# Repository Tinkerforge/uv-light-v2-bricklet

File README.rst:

UV Light Bricklet 2.0
=====================

This repository contains the firmware source code and the hardware design
files. The documentation generator configs can be found at
https://github.com/Tinkerforge/generators

Repository Content
------------------

software/:
 * examples/: Examples for all supported languages
 * build/: Compiled files
 * src/: Source code of firmware
 * Makefile: Makefile to build project

hardware/:
 * Contains KiCad project files and additionally schematics as PDF

datasheets/:
 * Contains datasheets for sensors and complex ICs that are used

Hardware
--------

The hardware is designed with the open source EDA Suite KiCad
(http://www.kicad.org). Before you are able to open the files,
you have to install the Tinkerforge kicad-libraries
(https://github.com/Tinkerforge/kicad-libraries). You can either clone
them directly in hardware/ or clone them in a separate folder and
symlink them into hardware/
(ln -s kicad_path/kicad-libraries project_path/hardware). After that you
can open the .pro file in hardware/ with KiCad and from there view and
modify the schematics and the PCB layout.

Software
--------

If you want to do your own Brick/Bricklet firmware development we highly
recommend that you use our build environment setup script and read the
tutorial (https://www.tinkerforge.com/en/doc/Tutorials/Tutorial_Build_Environment/Tutorial.html).

To compile the C code we recommend you to install the newest GNU Arm Embedded
Toolchain (https://launchpad.net/gcc-arm-embedded/+download).
You also need to install bricklib2 (https://github.com/Tinkerforge/bricklib2).

You can either clone it directly in software/src/ or clone it in a
separate folder and symlink it into software/src/
(ln -s bricklib_path/bricklib2 project_path/software/src/). Finally make sure to
have CMake installed (http://www.cmake.org/cmake/resources/software.html).

After that you can build the firmware by invoking make in software/.
The firmware (.zbin) can then be found in software/build/ and uploaded
with brickv (click button "Flashing" on start screen).

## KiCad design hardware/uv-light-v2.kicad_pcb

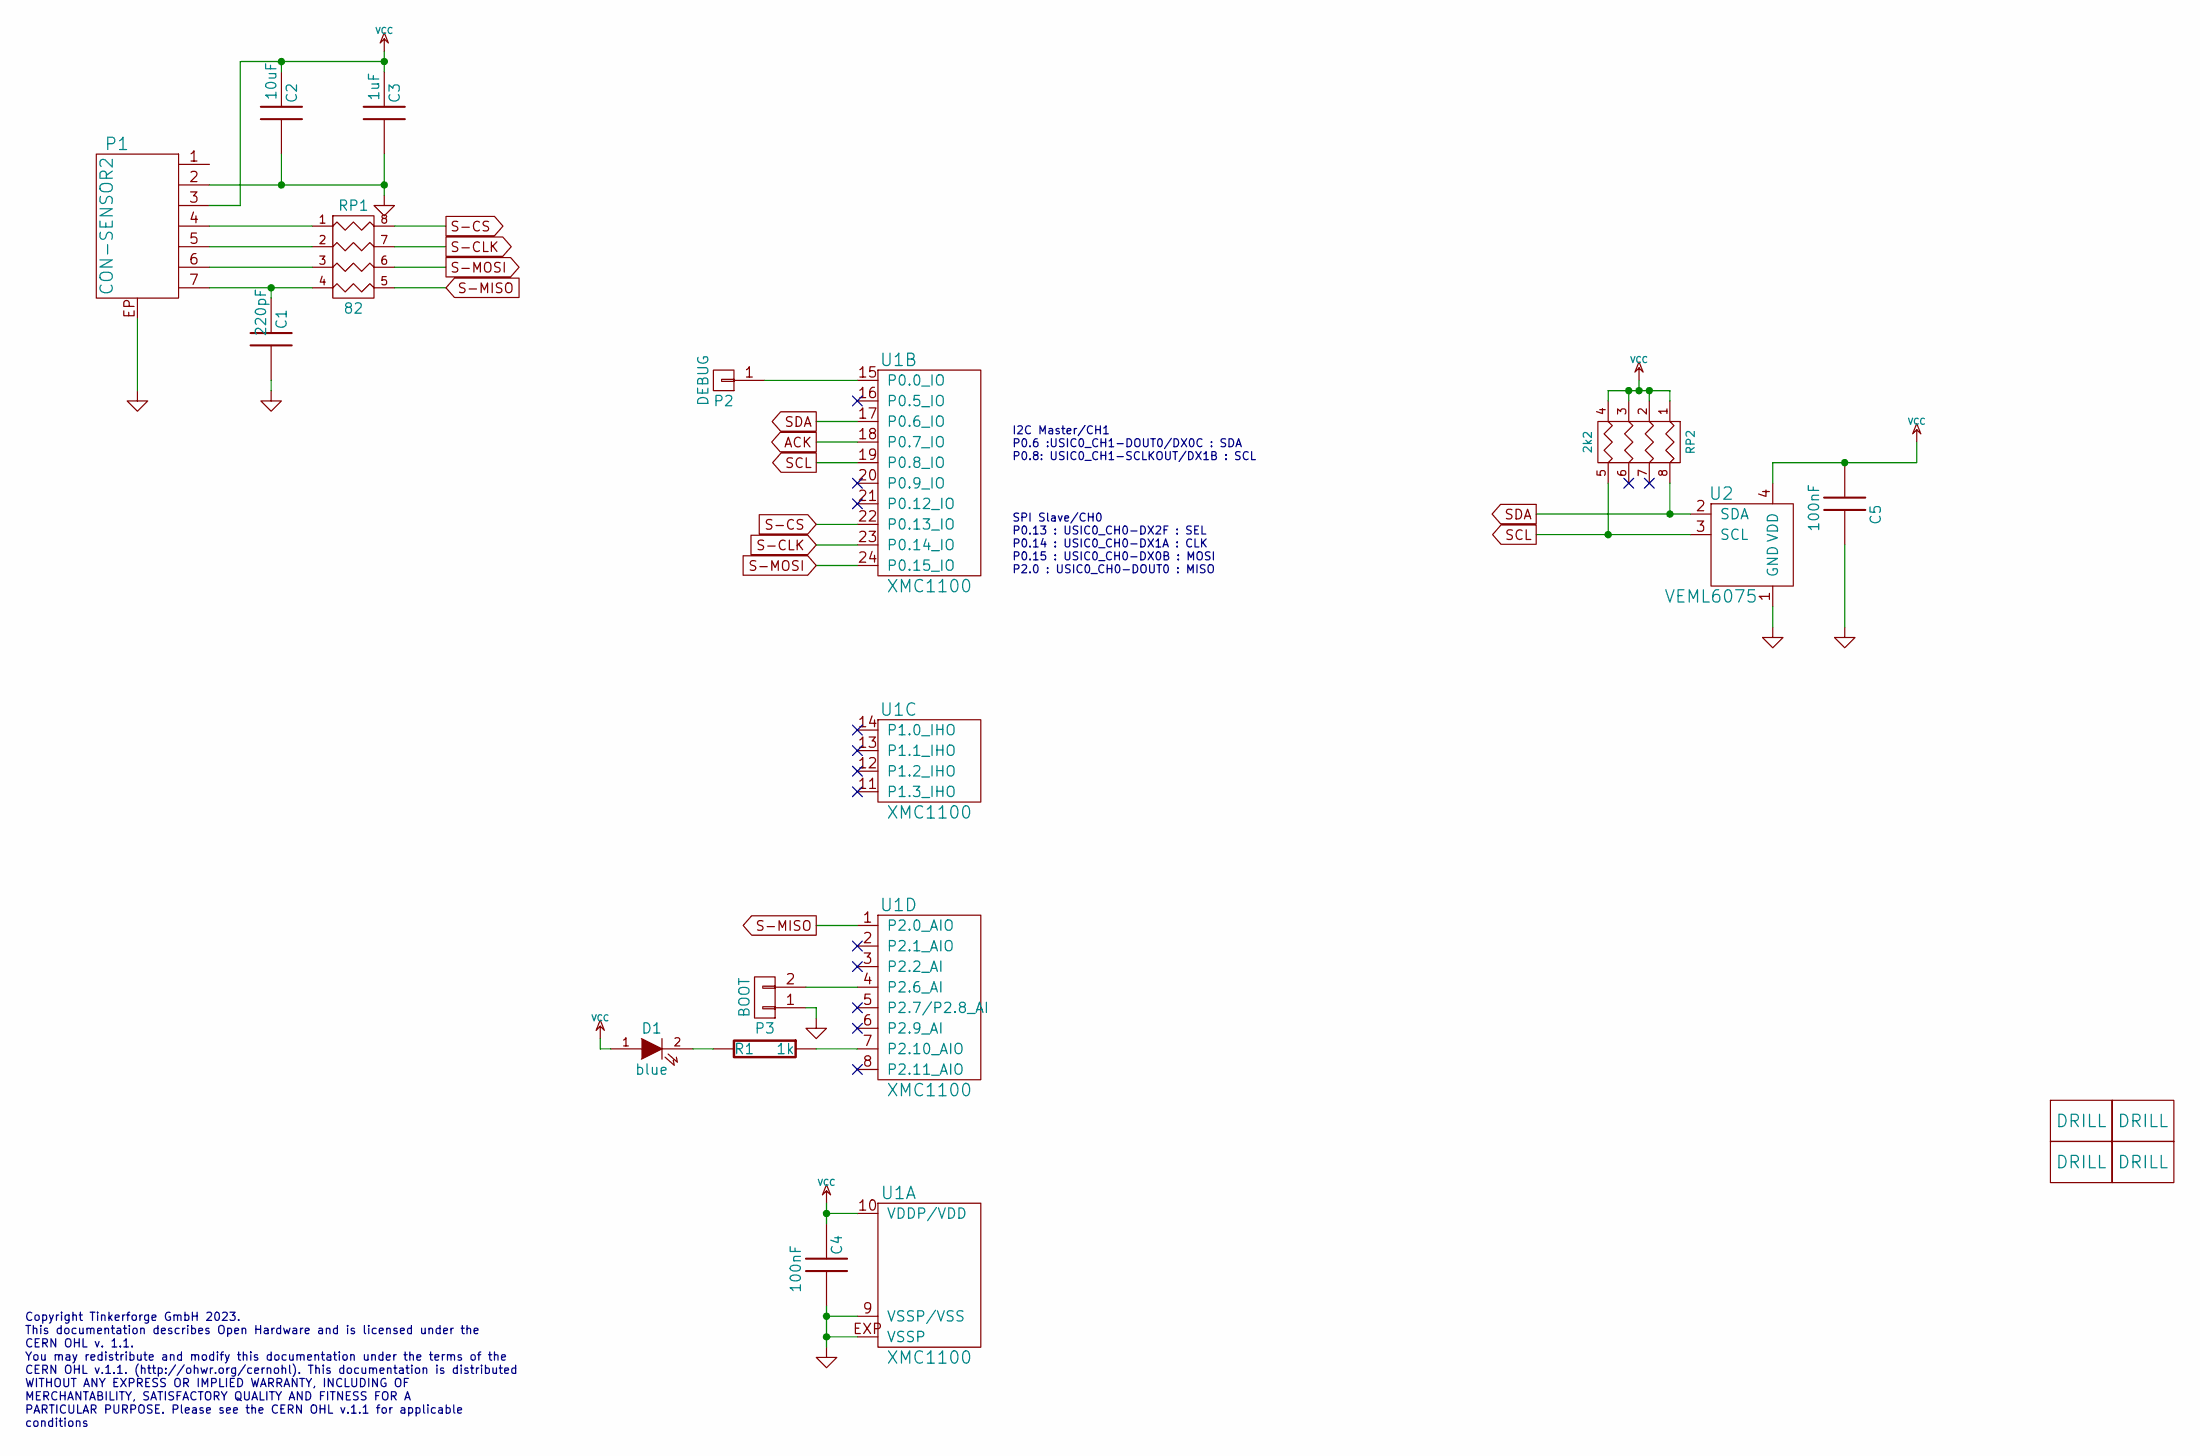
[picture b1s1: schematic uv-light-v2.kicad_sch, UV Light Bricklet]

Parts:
C1: 220pF; C0402F
C2: 10uF; C0805
C3: 1uF; C0603F
C4, C5: 100nF; C0603F
D1: blue; D0603F
P1: CON-SENSOR2
P2: DEBUG; DEBUG_PAD
P3: BOOT; SolderJumper
R1: 1k; R0603F
RP1: 82; 4X0402
RP2: 2k2; 0603X4
U1: XMC1100; QFN24-4x4mm-0.5mm
U2: VEML6075; OPLGA4
U3, U4, U5, U6: DRILL; DRILL_NP

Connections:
ACK: U1.18 (P0.7_IO)
GND: C1.1, C2.1, C3.1, C4.1, C5.1, P1.2, P1.EP, P3.1, U1.9 (VSSP/VSS), U1.EXP (VSSP), U2.1 (GND)
unnamed: C1.2, P1.7, RP1.4
unnamed: D1.2 (K), R1.2
unnamed: P1.4, RP1.1
unnamed: P1.5, RP1.2
unnamed: P1.6, RP1.3
unnamed: P2.1, U1.15 (P0.0_IO)
unnamed: P3.2, U1.4 (P2.6_AI)
unnamed: R1.1, U1.7 (P2.10_AIO)
S-CLK: RP1.7 (R2), U1.23 (P0.14_IO)
S-CS: RP1.8 (R1), U1.22 (P0.13_IO)
S-MISO: RP1.5 (R4), U1.1 (P2.0_AIO)
S-MOSI: RP1.6 (R3), U1.24 (P0.15_IO)
SCL: RP2.5 (R4), U1.19 (P0.8_IO), U2.3 (SCL)
SDA: RP2.8 (R1), U1.17 (P0.6_IO), U2.2 (SDA)
VCC: C2.2, C3.2, C4.2, C5.2, D1.1 (A), P1.3, RP2.1, RP2.2, RP2.3, RP2.4, U1.10 (VDDP/VDD), U2.4 (VDD)

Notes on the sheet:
I2C Master/CH1 P0.6 :USIC0_CH1-DOUT0/DX0C : SDA P0.8: USIC0_CH1-SCLKOUT/DX1B : SCL
SPI Slave/CH0 P0.13 : USIC0_CH0-DX2F : SEL P0.14 : USIC0_CH0-DX1A : CLK P0.15 : USIC0_CH0-DX0B : MOSI P2.0 : USIC0_CH0-DOUT0 : MISO
Copyright Tinkerforge GmbH 2023. This documentation describes Open Hardware and is licensed under the CERN OHL v. 1.1. You may redistribute and modify this documentation under the terms of the CERN OHL v.1.1. (http://ohwr.org/cernohl). This documentation is distributed WITHOUT ANY EXPRESS OR IMPLIE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

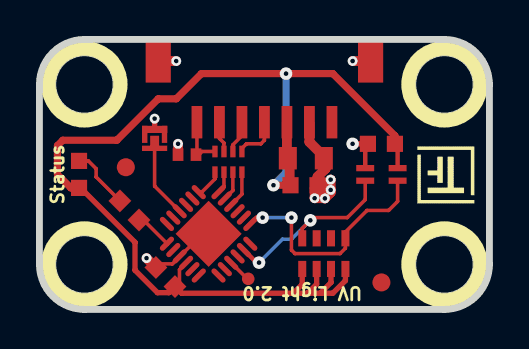
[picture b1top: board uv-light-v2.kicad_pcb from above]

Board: 2 copper layers, 25.0 x 15.0 mm, 22 parts (2 on the bottom side), 16 nets.

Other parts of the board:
Fiducial_Mark: VAL**; Fiducial_Mark
Fiducial_Mark#2: VAL**; Fiducial_Mark
VAL: CE_5mm
VAL#2: WEEE_7mm

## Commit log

2018-02-16 Add "in development" tag
2018-02-16 Add datasheets
2018-02-16 Add schematic
2018-02-16 Add layout
2018-02-16 Fix version number
2018-02-20 Add .gitignore
2018-02-20 Cleanup KiCad libraries config
    Ensure LibDir=kicad-libraries and LibName1=tinkerforge.
    Remove special library.
2018-03-13 Add "tinkerforge.com" to silkscreen
2018-03-16 change sensor to veml6075
2018-04-17 Initial firmware
2018-04-18 Update datasheet and application note
2018-04-20 Firmware implementation
2018-04-23 Change naming
2018-05-02 Fix deadly bug:
    "expected_fifo_level" can't be used in any FIFO ready state as detection
    of a ready state is based on expected FIFO level and it is set to zero after
    the detection.
2018-05-07 Move callback value type definition to config.h
2018-05-11 Rename files
2018-06-06 fix logos, fix origin
2018-06-06 Adapt to bricklib2 callback-value changes to fix wrong threshold min/max types
2018-06-18 Change capacitor footprint(s) to C0402F
2018-06-28 Fix readme
2018-07-11 Add Makefile with docker support
2018-07-11 Remove obsolete generate_makefile scripts
2018-07-11 Update directory structure and build instructions
2018-07-17 specify processor
2018-07-30 Use correct formula for applying the compensation values
    Add UVI getter/callback.
2018-07-30 Update datasheet
2018-07-30 Use correct UV responsivity values for 50ms integration time
2018-07-30 Only read values every 10ms
2018-07-30 Shorten some enum value names
2018-07-31 Add 3d model (*.FCStd & *.step)
2018-07-31 Add PDF schematic
2018-07-31 Add integration time configuration
2018-07-31 Turn off advanced printf mode to safe on flash space
2018-07-31 Check for sensor saturation and underflows
    Report saturation as -1.
    Also report UV readings in 1/10 mW/m² instead of 1/10 µW/cm².
2018-07-31 Remove unnecessary global buffer
2018-08-01 Use i2c fifo state machine for all states
    We use the i2c fifo state machine for all of the possible states
    to make sure that timeout errors are automatically handled internally.
2018-09-06 Add examples
2018-09-14 vbnet: Fix typo in comment
2018-10-02 Add BOOTLOADER_FIX_POINTER_END define
2018-10-04 Add rev to changelog
2018-10-16 Remove in-development marker
2018-11-06 Add rust examples
2018-11-07 rust: Accept host names for ip connection, fix naming inconsistencies
2018-11-07 rust: Rename callback receivers.
2018-12-14 Add go examples.
2018-12-14 go: Fix printf parameters.
2018-12-18 go: Change import path.
2018-12-18 go: Change import path again.
2018-12-20 rust: Reformat examples.
2019-01-24 mqtt: Add examples.
2019-01-24 mqtt: Fix example header.
2019-01-24 mqtt: Remove executable bit in example permissions.
2019-01-24 go: Minor example fixes.
2019-01-24 mqtt: Minor example fixes.
2019-03-28 mqtt: Fix whitespace.
2019-05-29 Increase version for new release (changes in bricklib2)
2019-08-22 c: Adapt to bindings changes
2020-01-13 examples: Use python3 input instead of python2 raw_input.
2020-01-13 examples: mqtt: Remove trailing whitespace.
2020-08-19 Add uc examples.
2020-08-25 uc: Fix whitespace
2020-08-27 uc: Fix warnings.
2020-09-02 uc: Add example driver note.
2020-10-16 uc: Fix divisor type.
2021-10-25 Update KiCad link
    https://www.kicad.org/blog/2021/10/Avoid-links-to-former-kicad-domain/
2022-04-19 examples: uc: Rename TF_HalContext to TF_HAL.
2022-04-27 uc: Adapt to bindings changes
2022-07-06 Add license files.
2023-01-27 fix schematic
2023-01-27 Data Cleanup

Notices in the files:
hardware/uv-light-v2.kicad_pcb:
Licensed under CERN OHL v.1.1
Copyright (©) 2023, T.Schneidermann
